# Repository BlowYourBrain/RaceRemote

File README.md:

# RaceRemote

Текущая сборка: [плата 0.3, отдельный общий провод XIAO и карта подключений](cad/xiao-return-h10/README.md).

Последняя примерка: [провода мотора и обнаруженный конфликт резерва клеммы с подвеской](cad/motor-harness/README.md).

Текущий вариант внутреннего питания: [CAD припаянной пары и крепления](cad/direct-logic-harness/README.md), включая ограничения прежней проводки.

Проект одинаковых радиоуправляемых машинок с управлением по Wi-Fi с телефона, сменными кузовами и опциональной камерой.

**Перед продолжением работы прочитайте [описание проекта и принятые решения](docs/project-brief.md).** Там собраны требования, имеющееся железо, результаты первичного аудита и вопросы, которые ещё предстоит решить.

**Ближайшие шаги к физической сборке:** [первый прототип](docs/first-prototype.md) — доступные устройства, недостающие данные и порядок радио/FPV, привода, механики и зарядки.

- [Стенд Android ↔ ESP32](docs/control-bench.md) — `vea.raceremote`, запуск и проверенные устройства.
- [Протокол Control v1](docs/control-v1.md) — команды, сессия и остановка.
- [Подготовка стенда привода](docs/drive-bench.md) — проект соединений TA6586, питание и проверка рулевого узла.
- [Контракты и их статус](docs/contracts.md) — согласованные требования и интерфейсы, которые предстоит определить.
- [Архитектура и known unknowns](docs/architecture-and-unknowns.md) — организация системы, открытые вопросы и способы их закрыть.
- [Кандидаты шасси](docs/chassis-candidates.md) — исходные проекты, ограничения и возможная адаптация под Wi-Fi.
- [Детали и цены](docs/parts.md) — предложения магазинов, количество на 1/4/6 машинок и незакрытые позиции.
- [Камера для FPV](docs/camera-candidates.md) — кандидаты и проверка задержки до выбора для серии.
- [Первый FPV-стенд](docs/fpv-bench.md) — состав, подключение и порядок измерений; предложение для покупки ещё подбирается.
- [USB-C: зарядка и прошивка](docs/usb-c-power.md) — отдельный удобный зарядный порт, ограничения для 2S и сервисный USB под кузовом.
- [Watchdog зарядного контроллера](hardware/charge-watchdog/README.md) — схема-кандидат и проверка удержания запрета при зависании MCU.
- [Зарядный MCU и согласование сигналов](hardware/charger-mcu/README.md) — CH32, аппаратный ARM/revoke/readback и доступ SWIO; схема без программы и монтажа.
- [Удерживаемая ошибка зарядного тока](hardware/charge-overcurrent/README.md) — INA300 и шунт, схема стенда и границы проверки.
- [Смена батареи и кузов](docs/battery-and-body.md) — три LW 601844HP, быстрое снятие кузова на магнитах и зарядка запасной батареи.
- [Правила работы агента](AGENTS.md) — обязательная фиксация ключевых моментов и контрактов по просьбе пользователя.

Репозитории:

- [RaceRemote](https://github.com/BlowYourBrain/RaceRemote) — Android-приложение и старые эксперименты с Arduino.
- [RC_CAR_ESP32](https://github.com/BlowYourBrain/RC_CAR_ESP32) — прошивка стенда ESP32 и старый эксперимент; приватный репозиторий.

Выбор серийных компонентов и электрическая схема пока не утверждены.

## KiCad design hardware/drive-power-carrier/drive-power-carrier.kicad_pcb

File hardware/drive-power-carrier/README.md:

# Общая плата привода и питания XIAO — предложение 0.3

**0.3, 15 сентября:** добавлена отдельная площадка H10 для общего провода XIAO; H5 остаётся силовым возвратом входного питания. Схема/PCB проходят ERC, DRC и parity: 26 позиций, 58 выводов, семь подмен цепей. Прежние 57 площадок и дорожки версии 0.2 сохранены, зоны меди пересчитаны. [Отчёт v03](../../docs/evidence/drive-power-carrier-v03/summary.json), [текущая проводка и карта площадок](../../cad/xiao-return-h10/README.md). Геометрическая проверка H10 и нового провода пройдена при 0/+3; ток/нагрев и физический монтаж не проверены. Ниже сведения о конструкции 0.2 остаются основанием; её отчёты исторические в `957e015`.

15 сентября 2026. Контракт **DRIVE-POWER-CARRIER-01 v0.2**. Это отдельный кандидат объединения [носителя TA6586](../motor-carrier/README.md) и [XIAO-LOGIC-01 v0.2](../xiao-logic-power/README.md). В 0.2 исправлены [площадки MAX40200 и резерв его корпуса](max40200-package.md); уведомление 2571C оказалось изменением транспортной упаковки. Исходные схемы сохранены. Изготовления, монтажа и физических испытаний ещё нет.

[Схема PDF](schematic.pdf) · [редактируемая схема](drive-power-carrier.kicad_sch) · [PCB KiCad](drive-power-carrier.kicad_pcb) · [верх](top.svg) · [низ, зеркальный вид](bottom.svg) · [BOM](bom.csv) · [все выводы](connections.csv) · [3D в машинке](../../cad/drive-power-carrier/viewer.html).

Размер PCB остался **30 × 18 × 1,6 мм**. Сохранились места всех 14 прежних позиций и геометрия их 27 площадок. Новые U2/U3, делитель и конденсаторы находятся снизу; нагрузочный R7 — сверху. Два прежних отрезка VM заменены обходом четырёх тепловых переходов U2. Остальные прежние дорожки сохранены. Вместо отдельной платы питания получилась одна плата с 25 позициями: 16 покупных компонентов и девять встроенных площадок для проводов.

| Площадка | Цепь и назначение |
|---|---|
| H1 / H2 | CMD_FI / CMD_BI: команды TA6586 через прежние резисторы |
| H3 / H5 | DRIVE_GND: общий провод привода и логики, не произвольная земля зарядника |
| H4 | VM: отдельно квалифицируемое питание мотора |
| H6 / H7 | FO / BO: выводы мотора |
| H8, новая | WAVE_5V: вход от Waveshare, условный расчётный диапазон 4,75…5,25 В |
| H9, новая | XIAO_BAT: выход через MAX40200 к BAT0 XIAO; не к выводу 5V/VBUS |
| H10, добавлена в 0.3 | DRIVE_GND: отдельная посадка провода GND0 XIAO; H5 освобождена для силового возврата |

Участники питания: Waveshare → U2 TPS73701DRBR → U3 MAX40200AUK+T → BAT0 XIAO. Общий провод XIAO/Waveshare приходит к DRIVE_GND. VM, WAVE_5V и XIAO_BAT — разные цепи. К новой плате не добавлен провод штатного USB VBUS. Сырой аккумулятор 2S нельзя подключать к H8/H9; объединение минусов батареи, защиты и USB зарядки требует отдельной согласованной схемы. Эта плата не заряжает LW и не заменяет его защиту.

Схема логики электрически повторяет v0.2 с перенумерацией: прежние U1/U2 → U2/U3; R1…R3 → R5…R7; C1…C4 → C3…C6; J1/J3 → H8/H9. Земляные J2/J5 заменены существующими H3/H5. U2 выдаёт номинально 3,997 В; R7=360 Ом обеспечивает предварительную нагрузку до обратного блокиратора. Для C4 требуется фактическая ёмкость ≥1 мкФ, для C5/C6 ≥0,33 мкФ каждого, полная ёмкость на выходе U3 ≤100 мкФ. Конкретные MLCC и их зависимость от напряжения ещё не выбраны.

При исчезновении питания логики аппаратная остановка здесь не доказана: сохраняются резисторы на входах TA6586 и программные правила остановки, но последовательность спадания шин, USB-переходы и ток мотора требуют стенда. MAX40200 имеет внутреннюю обратную блокировку; её реальные переходы и отказы платы пока не проверены.

Проверки KiCad 10.0.6: **ERC=0, DRC=0, несоединённых цепей=0, расхождений схемы и платы=0**. Независимый список сверяет 57 выводов, включая четыре NC, и 12 рабочих цепей; шесть намеренных подмен цепей обнаружены. Координаты CAD сверены с площадками и центрами новых компонентов PCB; размеры/шаг площадок U3 — с прочитанным чертежом. [Отчёт и хеши](../../docs/evidence/drive-power-carrier-v02/summary.json), [DRC с перечнем стандартно отключённых проверок](../../docs/evidence/drive-power-carrier-v02/drc.json). Это проверка проекта при выбранных правилах, не подтверждение его допустимого тока. Отчёты v01 относятся к прежней геометрии `c041b2b`.

Разводка предлагает минимальный зазор/ширину 0,15 мм, силовые дорожки прежнего носителя — 1,2 мм, новые основные линии питания — 0,4…0,6 мм. Четыре перехода под тепловой площадкой U2 имеют отверстие 0,3 мм и диаметр меди 0,6 мм. Изготовитель, толщина меди, обработка переходов, маска/паста и ручной монтаж не согласованы. Gerber для заказа не выпущен.

Открытые вопросы перед изготовлением:

- U2 DRB: посадка основана на TI Rev W, стр. 47–48; тепловая площадка обязательна. Заполнение/закрытие переходов и объём припоя нужно согласовать, иначе припой может уйти в отверстия.
- U3: корпус сверён с официальным 21-0057 K, площадки — с копией Maxim 90-0174 B. Актуальность редакции рисунка площадок у ADI и посадка реального компонента ещё не подтверждены. PIN2571C касается только транспортной упаковки.
- Тепло двух микросхем рядом с моторным драйвером. Прежний условный расчёт даёт около 0,513 Вт на проходном элементе U2 при 0,5 А и до 0,850 Вт в выбранном углу при 0,6 А, без собственного тока и переходных процессов. Сам факт наличия меди/переходов не доказывает допустимую температуру.
- Стабильность питания при работе камеры, пусках мотора/серво и подключении USB; реальные токи и допустимая нагрузка дорожек.
- Новые провода H8/H9, разгрузка пайки, установка/снятие платы и остальные положения регулировки.

Источники геометрии: [TPS737, TI Rev W](https://www.ti.com/lit/ds/symlink/tps737.pdf), [MAX40200, ADI Rev 4](https://www.analog.com/media/en/technical-documentation/data-sheets/max40200.pdf); исходные электрические расчёты и ограничения переноса падения напряжения SOT23 с 3,3 В на около 4 В — в [XIAO-LOGIC-01 v0.2](../xiao-logic-power/README.md). Новых цен и заказов этот BOM не подтверждает; имеющиеся ценовые наблюдения остаются в [таблице деталей](../../docs/parts.md).

Воспроизведение из корня репозитория, локальным Python KiCad:

```powershell
& build/tooling/kicad-10.0.6/bin/python.exe tools/build_drive_power_carrier.py
& build/tooling/kicad-10.0.6/bin/python.exe tools/verify_drive_power_carrier.py
uv run --with-requirements tools/cad-candidate-requirements.txt python tools/check_drive_power_fit.py
uv run --with-requirements tools/cad-candidate-requirements.txt python tools/build_drive_power_view.py
```

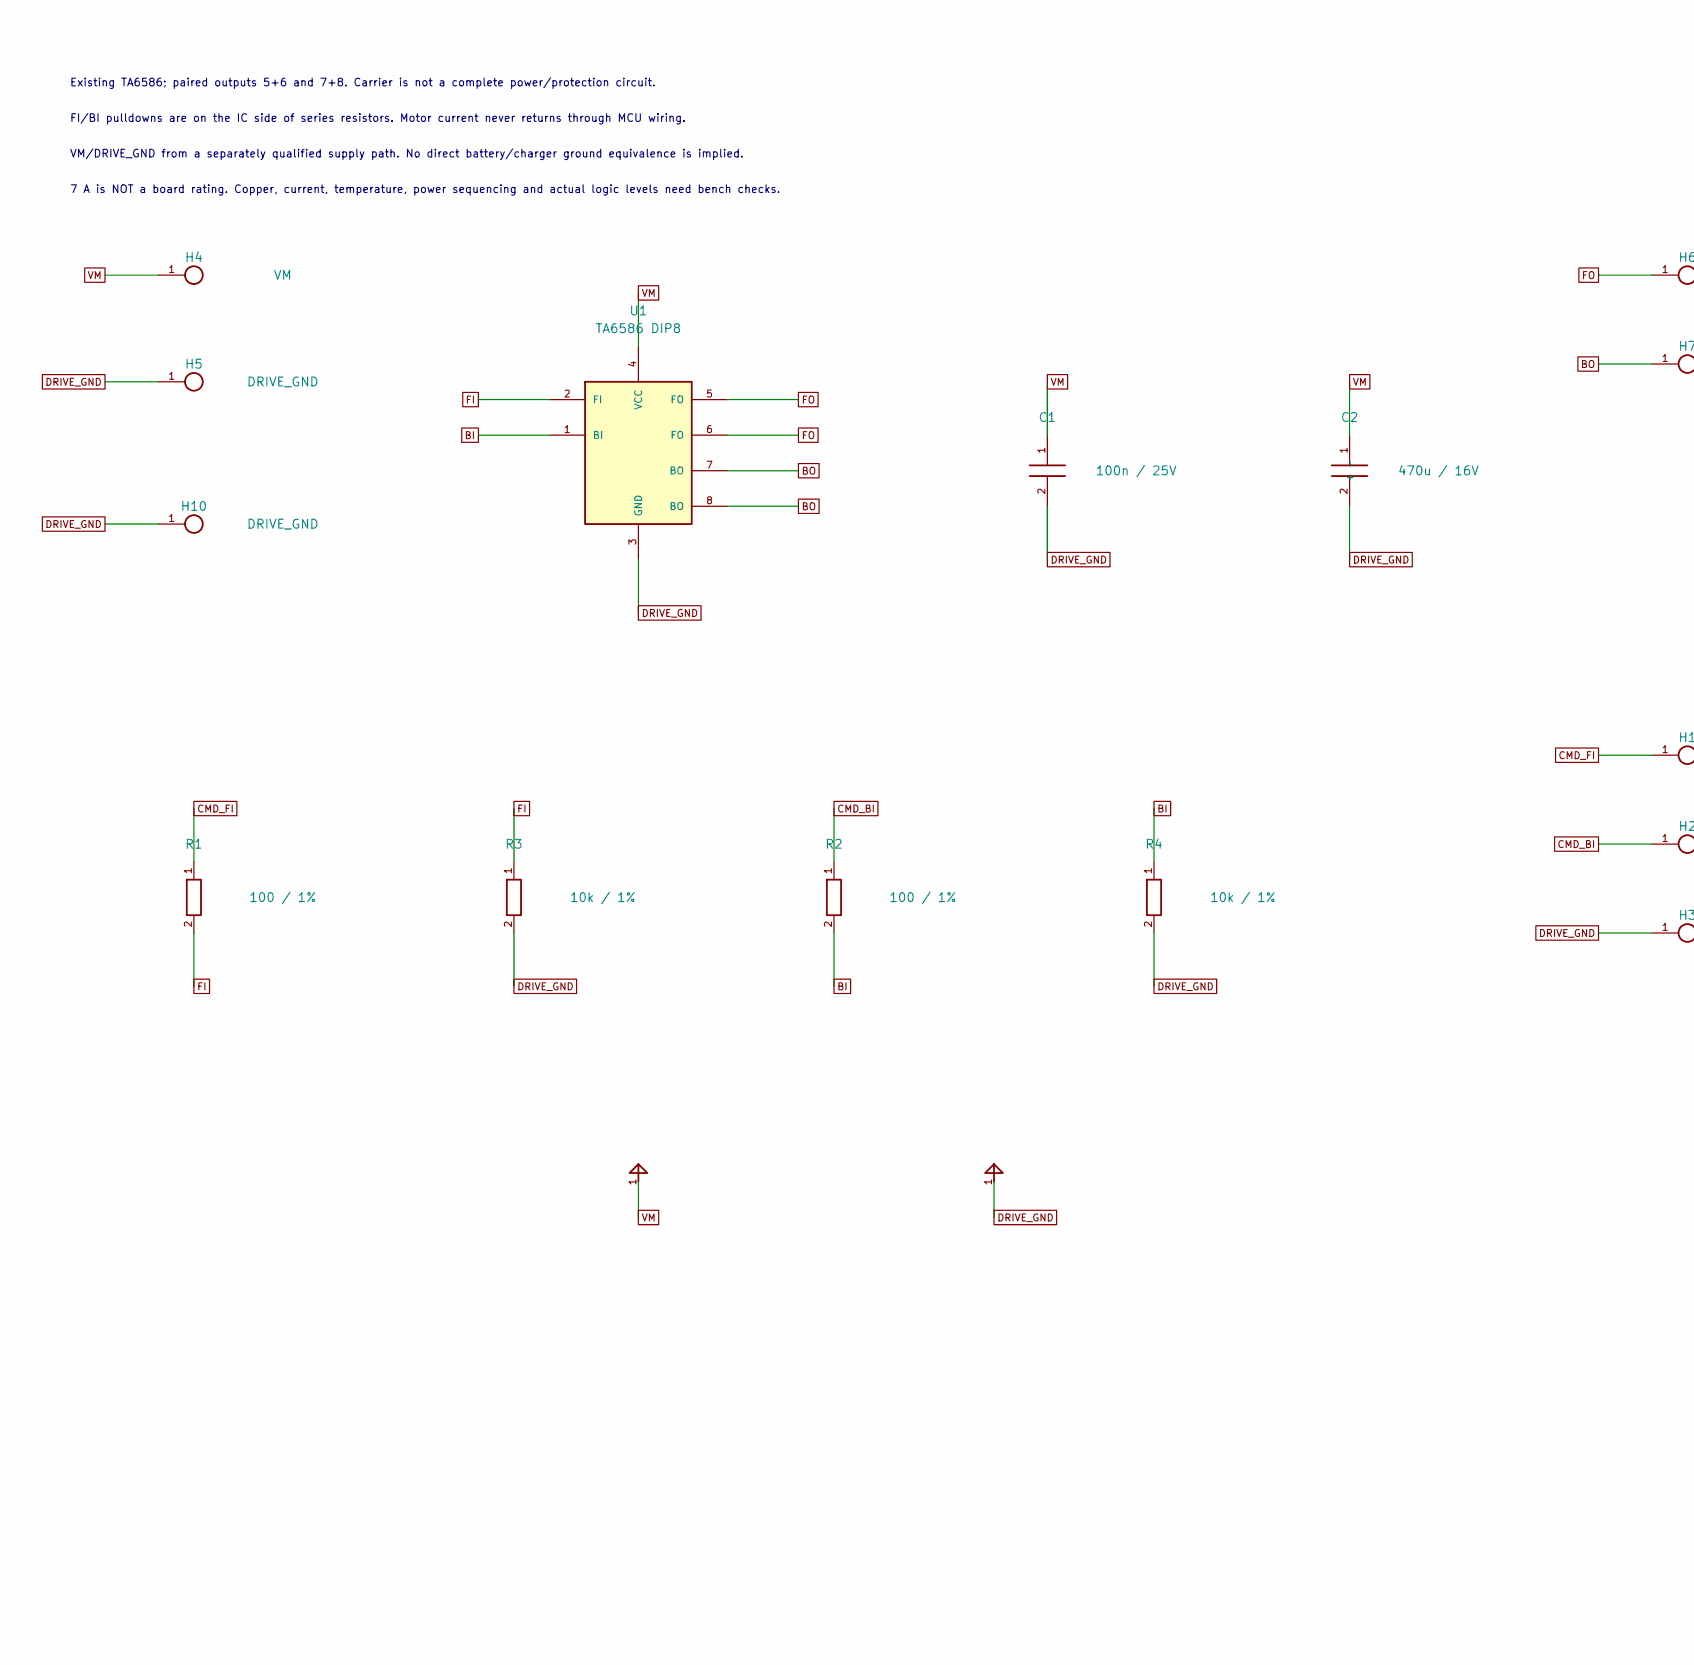
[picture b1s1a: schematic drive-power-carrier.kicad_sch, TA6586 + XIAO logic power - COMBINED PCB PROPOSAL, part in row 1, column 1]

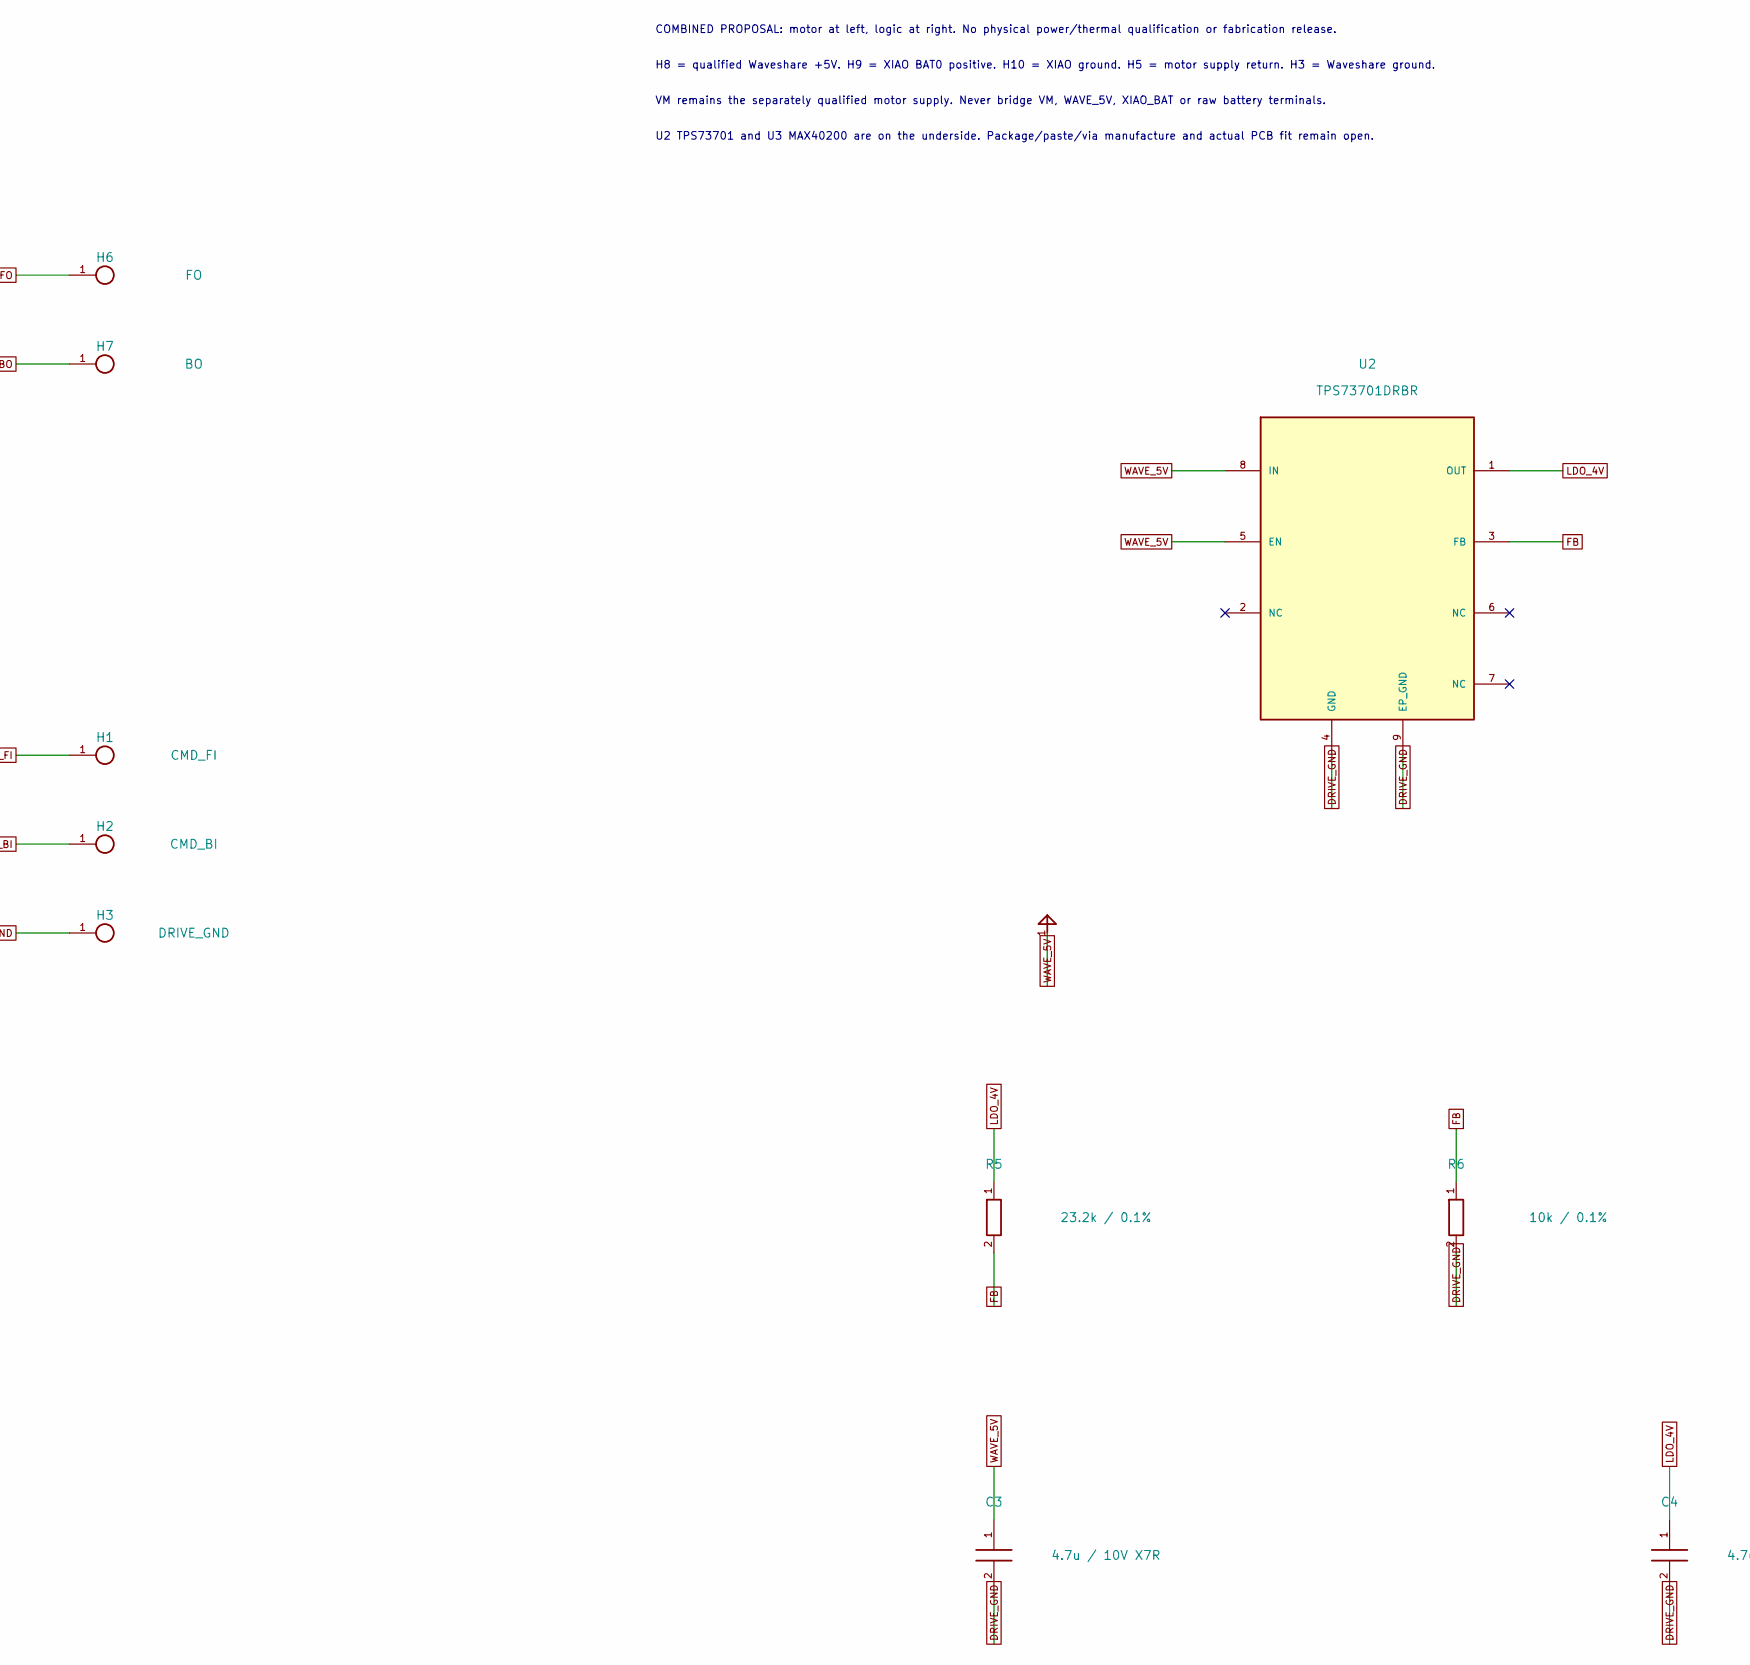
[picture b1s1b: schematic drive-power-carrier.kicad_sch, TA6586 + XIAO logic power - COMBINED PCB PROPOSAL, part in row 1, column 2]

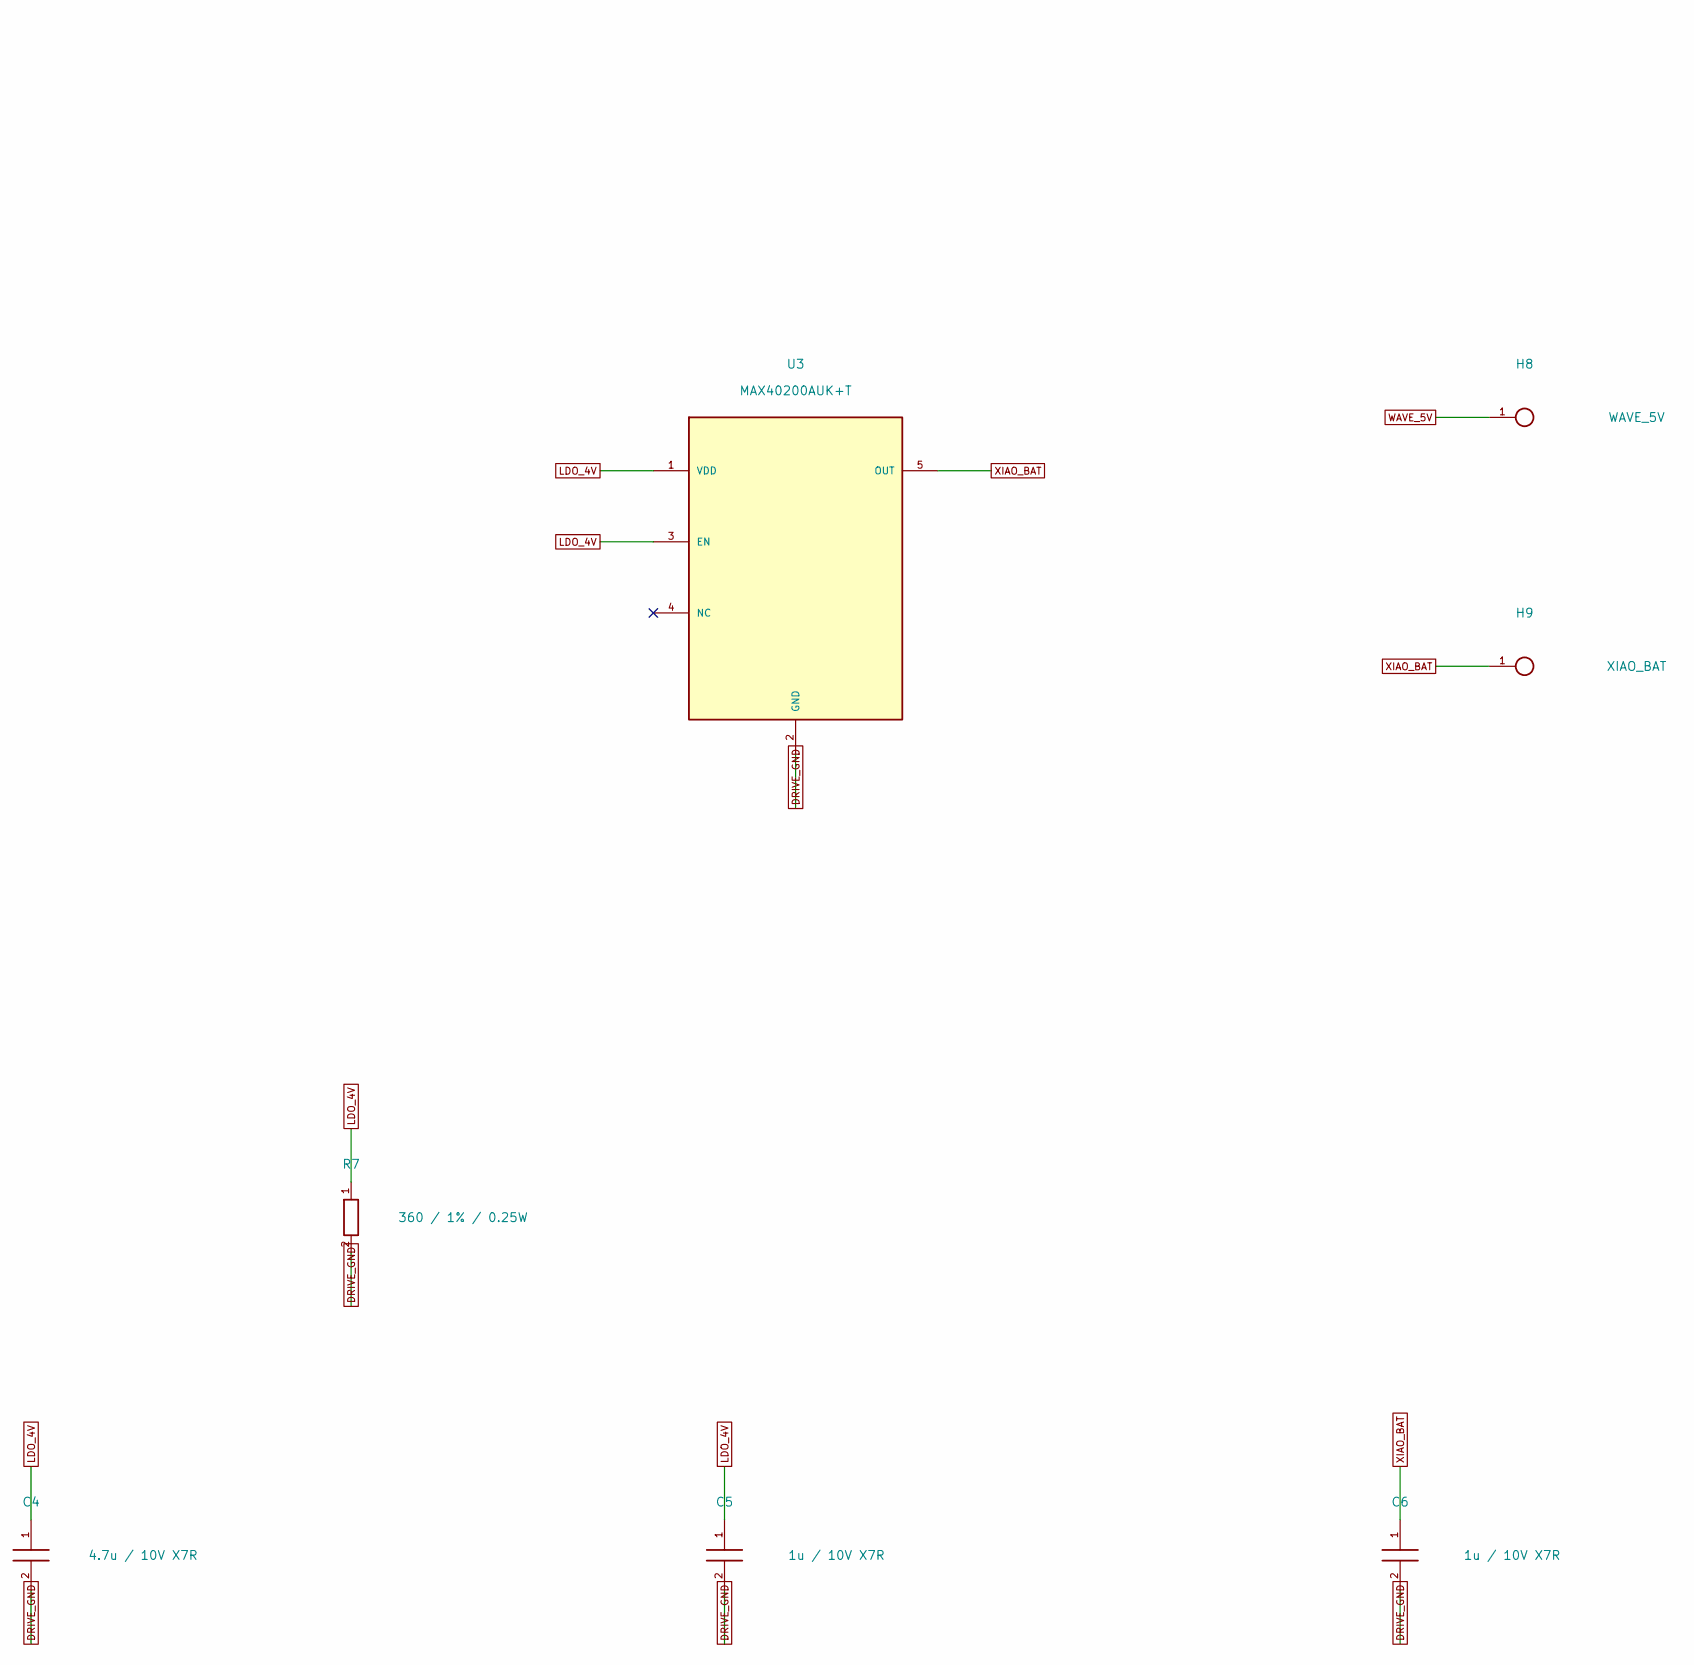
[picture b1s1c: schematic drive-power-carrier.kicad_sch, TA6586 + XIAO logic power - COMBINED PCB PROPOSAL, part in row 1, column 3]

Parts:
C1: 100n / 25V; C_0805
C2: 470u / 16V; CP_D8_P3.5
C3: 4.7u / 10V X7R; C_0805_C3
C4: 4.7u / 10V X7R; C_0805_C4
C5: 1u / 10V X7R; C_0805_C5
C6: 1u / 10V X7R; C_0805_C6
H1: CMD_FI; WirePad_1mm
H2: CMD_BI; WirePad_1mm
H3, H5: DRIVE_GND; WirePad_1mm
H4: VM; WirePad_1mm
H6: FO; WirePad_1mm
H7: BO; WirePad_1mm
H8: WAVE_5V; WirePad_1mm_H8
H9: XIAO_BAT; WirePad_1mm_H9
H10: DRIVE_GND; WirePad_1mm_H10
R1, R2: 100 / 1%; R_0805
R3, R4: 10k / 1%; R_0805
R5: 23.2k / 0.1%; R_0805_R5
R6: 10k / 0.1%; R_0805_R6
R7: 360 / 1% / 0.25W; R_1206_R7
U1: TA6586 DIP8; TA6586_DIP8
U2: TPS73701DRBR; TPS73701_DRB_3x3_EP_U2
U3: MAX40200AUK+T; SOT23_5_ADI_90_0174_B_U3

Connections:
BI: R2.2, R4.1, U1.1 (BI)
BO: H7.1, U1.7 (BO), U1.8 (BO)
CMD_BI: H2.1, R2.1
CMD_FI: H1.1, R1.1
DRIVE_GND: C1.2, C2.2 (-), C3.2, C4.2, C5.2, C6.2, H3.1, H5.1, H10.1, R3.2, R4.2, R6.2, R7.2, U1.3 (GND), U2.4 (GND), U2.9 (EP_GND), U3.2 (GND)
FB: R5.2, R6.1, U2.3 (FB)
FI: R1.2, R3.1, U1.2 (FI)
FO: H6.1, U1.5 (FO), U1.6 (FO)
LDO_4V: C4.1, C5.1, R5.1, R7.1, U2.1 (OUT), U3.1 (VDD), U3.3 (EN)
VM: C1.1, C2.1 (+), H4.1, U1.4 (VCC)
WAVE_5V: C3.1, H8.1, U2.5 (EN), U2.8 (IN)
XIAO_BAT: C6.1, H9.1, U3.5 (OUT)

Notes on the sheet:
Existing TA6586; paired outputs 5+6 and 7+8. Carrier is not a complete power/protection circuit.
FI/BI pulldowns are on the IC side of series resistors. Motor current never returns through MCU wiring.
VM/DRIVE_GND from a separately qualified supply path. No direct battery/charger ground equivalence is implied.
7 A is NOT a board rating. Copper, current, temperature, power sequencing and actual logic levels need bench checks.
COMBINED PROPOSAL: motor at left, logic at right. No physical power/thermal qualification or fabrication release.
H8 = qualified Waveshare +5V. H9 = XIAO BAT0 positive. H10 = XIAO ground. H5 = motor supply return. H3 = Waveshare ground.
VM remains the separately qualified motor supply. Never bridge VM, WAVE_5V, XIAO_BAT or raw battery terminals.
U2 TPS73701 and U3 MAX40200 are on the underside. Package/paste/via manufacture and actual PCB fit remain open.

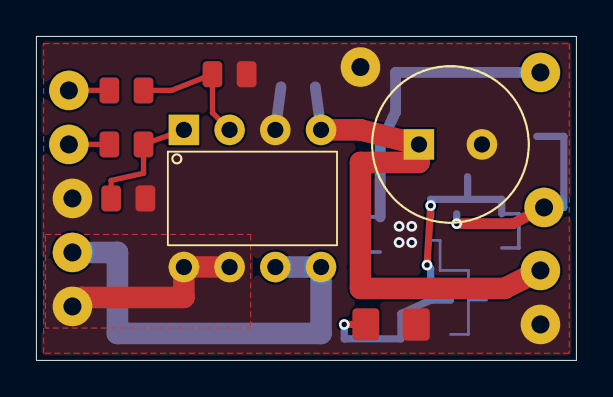
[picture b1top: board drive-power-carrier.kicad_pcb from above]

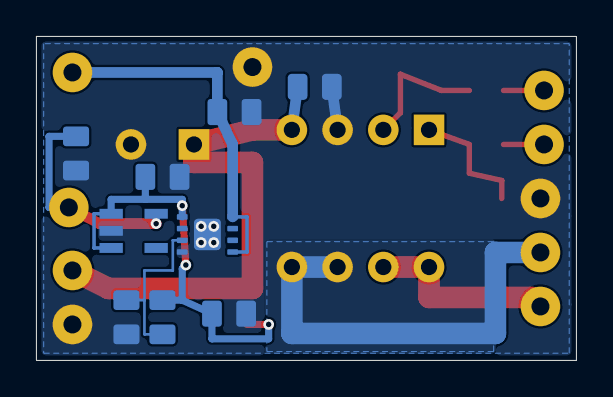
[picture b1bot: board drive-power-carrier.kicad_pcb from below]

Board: 2 copper layers, 30.0 x 18.0 mm, 26 parts (9 on the bottom side), 12 nets.

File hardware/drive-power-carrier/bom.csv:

reference,value,footprint,side,mpn_reference,status
C1,100n / 25V,RaceRemote_Motor:C_0805,B,,Candidate; not purchased
C2,470u / 16V,RaceRemote_Motor:CP_D8_P3.5,F,16ZLH470MEFC8X11.5,Candidate; not purchased
C3,4.7u / 10V X7R,RaceRemote_DrivePower:C_0805_C3,B,,Candidate; not purchased
C4,4.7u / 10V X7R,RaceRemote_DrivePower:C_0805_C4,B,,Candidate; not purchased
C5,1u / 10V X7R,RaceRemote_DrivePower:C_0805_C5,B,,Candidate; not purchased
C6,1u / 10V X7R,RaceRemote_DrivePower:C_0805_C6,B,,Candidate; not purchased
H1,CMD_FI,RaceRemote_Motor:WirePad_1mm,F,,Integral PCB solder pad; not purchased connector
H10,DRIVE_GND,RaceRemote_DrivePower:WirePad_1mm_H10,F,,Integral PCB solder pad; not purchased connector
H2,CMD_BI,RaceRemote_Motor:WirePad_1mm,F,,Integral PCB solder pad; not purchased connector
H3,DRIVE_GND,RaceRemote_Motor:WirePad_1mm,F,,Integral PCB solder pad; not purchased connector
H4,VM,RaceRemote_Motor:WirePad_1mm,F,,Integral PCB solder pad; not purchased connector
H5,DRIVE_GND,RaceRemote_Motor:WirePad_1mm,F,,Integral PCB solder pad; not purchased connector
H6,FO,RaceRemote_Motor:WirePad_1mm,F,,Integral PCB solder pad; not purchased connector
H7,BO,RaceRemote_Motor:WirePad_1mm,F,,Integral PCB solder pad; not purchased connector
H8,WAVE_5V,RaceRemote_DrivePower:WirePad_1mm_H8,F,,Integral PCB solder pad; not purchased connector
H9,XIAO_BAT,RaceRemote_DrivePower:WirePad_1mm_H9,F,,Integral PCB solder pad; not purchased connector
R1,100 / 1%,RaceRemote_Motor:R_0805,F,,Candidate; not purchased
R2,100 / 1%,RaceRemote_Motor:R_0805,F,,Candidate; not purchased
R3,10k / 1%,RaceRemote_Motor:R_0805,F,,Candidate; not purchased
R4,10k / 1%,RaceRemote_Motor:R_0805,F,,Candidate; not purchased
R5,23.2k / 0.1%,RaceRemote_DrivePower:R_0805_R5,B,,Candidate; not purchased
R6,10k / 0.1%,RaceRemote_DrivePower:R_0805_R6,B,,Candidate; not purchased
R7,360 / 1% / 0.25W,RaceRemote_DrivePower:R_1206_R7,F,,Candidate; not purchased
U1,TA6586 DIP8,RaceRemote_Motor:TA6586_DIP8,F,TA6586,Existing inventory
U2,TPS73701DRBR,RaceRemote_DrivePower:TPS73701_DRB_3x3_EP_U2,B,TPS73701DRBR,Candidate; not purchased
U3,MAX40200AUK+T,RaceRemote_DrivePower:SOT23_5_ADI_90_0174_B_U3,B,MAX40200AUK+T,Candidate; not purchased

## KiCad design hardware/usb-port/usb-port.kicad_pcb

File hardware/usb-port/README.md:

# Пассивная плата зарядного USB-C, ревизия 0.2

14 сентября 2026. **Схема и разводка выполнены, ERC/DRC и сравнение схемы с PCB прошли, плата не изготовлена.** Это плата разъёма с двумя резисторами, подключаемая к отдельному зарядному узлу. Зарядного контроллера, защиты аккумулятора, ограничения входного тока и согласования PD/QC здесь нет. Батарею 2S к VBUS не подключать.

[Открыть PCB](usb-port.kicad_pcb) · [Проект KiCad](usb-port.kicad_pro) · [CAD-размещение](../../cad/usb-port-study.md) · [Проверка DRC](../../docs/evidence/usb-port-pcb-drc.json)

[Схема KiCad](usb-port.kicad_sch) · [Схема PDF](schematic.pdf) · [ERC](../../docs/evidence/usb-port-erc.json) · [Проверка соединений и намеренных ошибок](../../docs/evidence/usb-port-pcb-verification.json)

Плата двухслойная, **26×7,6×1 мм**. Медь 35 мкм предложена для изготовления и использована в CAD; полный стек слоёв с изготовителем ещё не согласован. Разъём GCT USB4105-GF-A сверху, R1/R2 5,1 кОм ±1% типоразмера 0603 снизу. Два отверстия Ø2,4 мм с зонами без меди радиусом 2,5 мм под металлический крепёж. Шесть площадок Ø1,6 с отверстиями Ø0,8 — для пайки жгута; разъём жгута/калибр провода пока не выбраны. Крепление должно разгружать жгут от натяжения, его конструкция ещё открыта.

При сверке с библиотекой обнаружено: в прежнем CAD при X входа 58,5 мм задние площадки USB выходили за плату на 0,33 мм. Сдвиг входа до X=59,1 мм даёт зазор меди до заднего края **0,27 мм**. Ширина платы в CAD увеличена с 22 до 26 мм для пайки жгута за пределами крепёжных зон. Передняя кромка PCB осталась X=58,5 мм: корпус разъёма выступает за неё на 0,6 мм; отдельный вырез под вход не потребовался. [Геометрия площадок и отверстий](geometry.json) экспортируется из KiCad в OpenSCAD.

## USB-PORT-01, предложение v0.2

Участники: зарядный USB-C ↔ плата порта ↔ жгут ↔ отдельный зарядник. Штатный сервисный USB XIAO к этой плате не подключается.

| Контакт | Цепь | Назначение |
| --- | --- | --- |
| H1 | VBUS | Вход от USB-источника; цель системы — 5 В. К защите/ограничителю входа зарядника |
| H2 | DP | A6/B6 разъёма, линия определения источника |
| H3 | CC1 | A5, отдельный R1 5,1 кОм на GND |
| H4 | GND | Общий провод USB и экран разъёма |
| H5 | DM | A7/B7 разъёма, линия определения источника |
| H6 | CC2 | B5, отдельный R2 5,1 кОм на GND |

На рисунках сверху вниз слева H1/H2/H3, справа H4/H5/H6. Низ показан **без зеркалирования** для сопоставления слоёв, а не как вид при перевороте платы. Сверять маркировку цепей в KiCad перед пайкой; маркировка выводов на самой плате пока не добавлена.

CC1 и CC2 не соединяются друг с другом. На основной плате допускаются только подходящие высокоомные входы измерения CC, в том числе при её обесточивании; вторая пара Rd недопустима. Их допустимые напряжения и защита ещё определить. Резисторы позволяют источнику обнаружить потребитель, но **не разрешают произвольный ток**. Определение доступного тока, защита от ESD/замыканий, запрет заряда при ошибках и защита от обратного питания остаются в проектировании зарядного узла. D+/D− разведены для определения источника; USB 2.0 передача данных, импеданс пары и высокоскоростной интерфейс не заявлены.

Обрыв жгута, одного Rd или неправильное распознавание источника должны приводить к запрету заряда либо к подтверждённому допустимому режиму основной платы. Здесь MCU/логики разрешения нет. При отключении VBUS заряд прекращает основной узел; сам порт не разрешает движение.

Основание для двух Rd: [Renesas, модель USB Type-C Source/Sink, рисунки 5–6](https://www.renesas.com/en/support/engineer-school/usb-power-delivery-03). Распиновка J1 — [GCT USB4105 B4](https://gct.co/files/drawings/usb4105.pdf). A8/B8 (SBU) оставлены без подключений.

## Проверка и её пределы

KiCad **10.0.6**: DRC с повторной заливкой зон — 0 нарушений и 0 неподключённых соединений. Заданные минимумы: дорожка/межцепной зазор 0,15 мм, зазор меди до края 0,20 мм, зазор до отверстия 0,15 мм, переход Ø0,50 с отверстием Ø0,25 мм. Зазор до отверстия выбран с учётом заводского посадочного места: там есть около 0,194 мм до направляющего отверстия. Возможности конкретного изготовителя ещё не подтверждены.

В отчётах сохранены стандартные отключённые проверки KiCad; у площадок жгута и крепёжных отверстий нет отдельных courtyard. Их механические зоны проверяются явно в PCB/CAD. Исключения для получения нуля не добавлялись. **ERC: 0 замечаний; сравнение схемы с PCB: 0 расхождений.** Дополнительно сверены 27 логических выводов экспортированного netlist с площадками PCB, включая повторные контакты питания и экрана. В отдельных копиях намеренно перепутан H3 с CC2 и удалён R1: сравнение обнаруживает соответственно `net_conflict` и `missing_footprint`.

Схема задаёт соединения самостоятельно, без чтения цепей PCB. Символ USB взят из KiCad 10.0.6, обозначение экрана адаптировано `SH` → `S1` под GCT; происхождение и изменения — в [NOTICE](SYMBOLS-NOTICE.md). Для A8/B8 созданы явные NC-цепи KiCad, проводников на них нет. R1: контакт 1 → GND, 2 → CC1; R2: 1 → CC2, 2 → GND. UUID связывают символы с посадочными местами. Изменение 0.2 затрагивает электрические метаданные PCB; расположение и размеры площадок/отверстий сохранены, 42 записи CAD проверены по текущей плате.

ERC/DRC не доказывают допустимый ток/нагрев, отсутствие дефектов пайки, стойкость к статике и работоспособность зарядки. Зарядный узел 2S, крепление жгута и физические измерения остаются открытыми.

Приёмка изготовленного образца: прозвонить пары силовых контактов и экран, отсутствие коротких между VBUS/GND/DP/DM/CC; проверить каждый Rd около 5,1 кОм (при отключённом заряднике). Затем проверить 5-В источник с ограничением тока и обе ориентации A–C/C–C, падение напряжения/нагрев при выбранном токе, крепление и жгут. Эти измерения не выполнены.

## Воспроизведение

Используется Python из KiCad, обычный Python не содержит `pcbnew`:

```powershell
& build/tooling/kicad-10.0.6/bin/python.exe tools/build_usb_port_pcb.py
& build/tooling/kicad-10.0.6/bin/python.exe tools/build_usb_port_schematic.py
& build/tooling/kicad-10.0.6/bin/python.exe tools/verify_usb_port.py
& build/tooling/kicad-10.0.6/bin/kicad-cli.exe sch export pdf hardware/usb-port/usb-port.kicad_sch -o hardware/usb-port/schematic.pdf
uv run --with-requirements tools/cad-requirements.txt python tools/build_usb_port_study.py
```

`verify_usb_port.py` запускает штатные ERC/DRC с `--schematic-parity`, проверяет все разделы JSON независимо от кода возврата CLI, сопоставляет netlist/PCB и проверяет две намеренные ошибки в `build/usb-port-pcb/negative-controls/`. На физические устройства скрипт не воздействует. Для просмотра схемы достаточно проектных библиотек; повторно извлекать полные библиотеки KiCad не нужно. Генератор формата схемы основан на [официальном описании KiCad](https://dev-docs.kicad.org/en/file-formats/sexpr-schematic/).

На этом ПК KiCad извлечён в игнорируемую папку `build/tooling/kicad-10.0.6` из [официального подписанного дистрибутива](https://kicad-downloads.s3.cern.ch/windows/stable/kicad-10.0.6-x86_64.exe). Проверена действительная подпись KICAD SERVICES CORPORATION. Системная установка не выполнялась. Извлечены `bin/*`, `lib/*`, `share/kicad/schemas/*`, `share/kicad/template/*`, `share/kicad/scripting/*` и используемый footprint резистора. На другом ПК можно использовать обычную установку KiCad 10.0.6, изменив пути.

Источники посадочных мест и лицензия — [NOTICE](RaceRemote_USB.pretty/NOTICE.md). Полная стоимость PCB/монтажа, производитель и жгут не выбраны. Разъём есть в [таблице предложений](../../docs/charge-parts.md); резисторы пока указаны как тип/номинал без проверенной цены. Заказов нет.

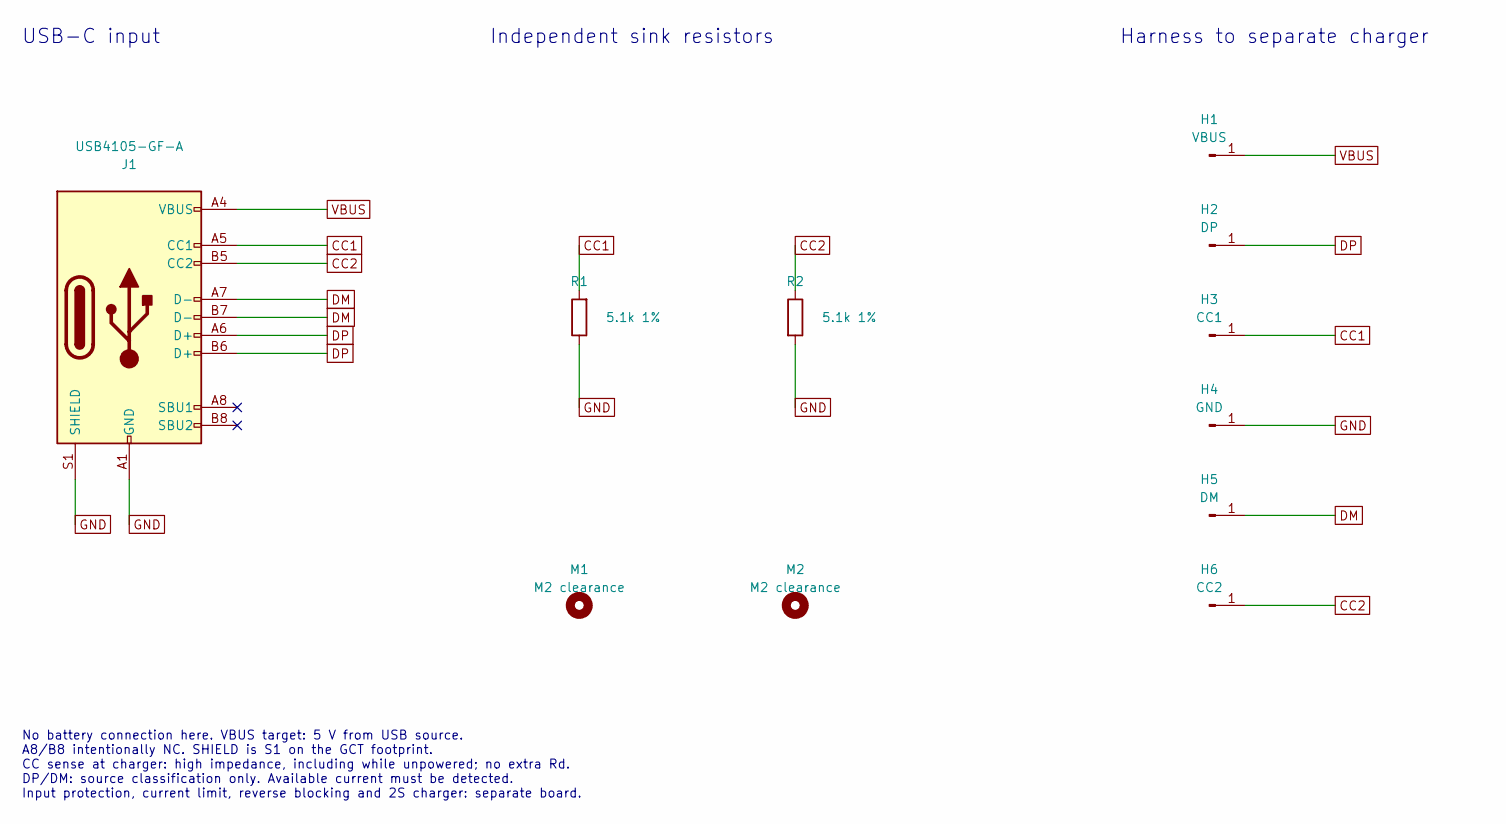
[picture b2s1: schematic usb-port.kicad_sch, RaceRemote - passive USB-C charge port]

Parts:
H1: VBUS; WirePad_D0.8mm
H2: DP; WirePad_D0.8mm
H3: CC1; WirePad_D0.8mm
H4: GND; WirePad_D0.8mm
H5: DM; WirePad_D0.8mm
H6: CC2; WirePad_D0.8mm
J1: USB4105-GF-A; USB_C_Receptacle_GCT_USB4105-xx-A_16P_TopMnt_Horizontal
M1, M2: M2 clearance; MountingHole_2.4mm
R1, R2: 5.1k 1%; R_0603_1608Metric

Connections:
CC1: H3.1, J1.A5 (CC1), R1.2
CC2: H6.1, J1.B5 (CC2), R2.1
DM: H5.1, J1.A7 (D-), J1.B7 (D-)
DP: H2.1, J1.A6 (D+), J1.B6 (D+)
GND: H4.1, J1.A1 (GND), J1.A12 (GND), J1.B1 (GND), J1.B12 (GND), J1.S1 (SHIELD), R1.1, R2.2
VBUS: H1.1, J1.A4 (VBUS), J1.A9 (VBUS), J1.B4 (VBUS), J1.B9 (VBUS)

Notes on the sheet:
USB-C input
Independent sink resistors
Harness to separate charger
No battery connection here. VBUS target: 5 V from USB source. A8/B8 intentionally NC. SHIELD is S1 on the GCT footprint. CC sense at charger: high impedance, including while unpowered; no extra Rd. DP/DM: source classification only. Available current must be detected. Input protection, current limi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

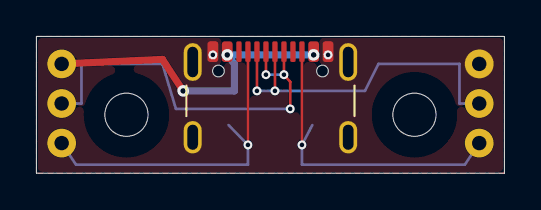
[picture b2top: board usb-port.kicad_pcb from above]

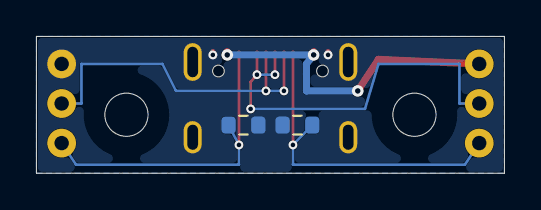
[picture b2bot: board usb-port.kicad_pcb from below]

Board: 2 copper layers, 26.0 x 7.6 mm, 11 parts (2 on the bottom side), 6 nets.

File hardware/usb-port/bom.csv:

Reference;Quantity_per_car;Description;Footprint;Purchase_status
J1;1;GCT USB4105-GF-A;USB_C_Receptacle_GCT_USB4105-xx-A_16P_TopMnt_Horizontal;Offers in docs/charge-parts.md - not ordered
R1 R2;2;5.1k ohm 1 percent 0603;R_0603_1608Metric;Exact manufacturer and offer unselected
PCB;1;2 layers 26x7.6 mm thickness 1 mm copper 35um;;Fabricator and cost unselected
H1 H2 H3 H4 H5 H6;0;Integrated solder pads - six wires required;;Wire specification and strain relief unselected
M1 M2;0;Integrated 2.4 mm mounting holes - M2 hardware required;;Screw length and nut type not finalized

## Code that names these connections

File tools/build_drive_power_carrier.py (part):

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        graphic(f, p.SHAPE_T_RECT, (x-w/2,y-h/2), (x+w/2,y+h/2), p.B_Fab if back else p.F_Fab)
        graphic(f, p.SHAPE_T_RECT, (x-w/2-margin,y-h/2-margin), (x+w/2+margin,y+h/2+margin), p.B_CrtYd if back else p.F_CrtYd, .05)
    u = new('U2', 'TPS73701DRBR', 20.5, 11, body=(3.1,3.1), height=1.05)
    mapping = {1:'LDO_4V',2:None,3:'FB',4:'DRIVE_GND',5:'WAVE_5V',6:None,7:None,8:'WAVE_5V'}
    for pin, dx, dy in [(1,1.4,-.975),(2,1.4,-.325),(3,1.4,.325),(4,1.4,.975),
                        (5,-1.4,.975),(6,-1.4,.325),(7,-1.4,-.325),(8,-1.4,-.975)]:
        pad(u,pin,mapping[pin],20.5+dx,11+dy,.6,.31)
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    # ADI 21-0057 K: D/E max3mm plus conservative .25mm protrusion each side.
    # Land pattern 90-0174 B: rectangular1.30x.55, row spacing2.50, pitch.95mm.
    u = new('U3','MAX40200AUK+T',24.6,10.8,body=(3.5,3.5),height=1.5)
    for pin,dx,dy,net in [(1,1.25,-.95,'LDO_4V'),(2,1.25,0,'DRIVE_GND'),(3,1.25,.95,'LDO_4V'),(4,-1.25,.95,None),(5,-1.25,-.95,'XIAO_BAT')]:
        pad(u,pin,net,24.6+dx,10.8+dy,1.3,.55)
    for a in u.Pads(): a.SetShape(p.PAD_SHAPE_RECT)
    outline(u,24.6,10.8,3.5,3.5,.25)
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
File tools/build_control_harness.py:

"""Route three proposed insulated control leads from referenced copper pads."""
import base64
import csv
import hashlib
import json
from pathlib import Path
import numpy as np
import trimesh
from build_packaging_v05 import mesh,intersect,tube
from layout_zcar_battery import box

ROOT=Path(__file__).resolve().parents[1]
DEST=ROOT/'cad/control-harness'
MOUNT=ROOT/'cad/motor-carrier-mount'


def main():
    reference=DEST/'xiao-pad-reference.json';pinref=json.loads(reference.read_text())
    pads={k:v['candidate_xyz_mm'] for k,v in pinref['pads'].items()}
    boardpath=ROOT/'hardware/motor-carrier/geometry.json';board=json.loads(boardpath.read_text())
    end={p['ref']:[25.75+p['xy_mm'][1],47+p['xy_mm'][0],31.1]for p in board['pads']if p['ref'].startswith('H')}
    routes={
      'FI':{'xiao':'D0','gpio':1,'terminal':'H1','net':'CMD_FI','color':[.9,.5,.05],
        'points_mm':[pads['D0'],[30.96583,87.1,23.17],[30.96583,87.1,37.3],[37.5,87.1,37.3],
                     [37.5,64,37.3],[28.75,64,37.3],[28.75,48.8,37.3],end['H1']]},
      'BI':{'xiao':'D1','gpio':2,'terminal':'H2','net':'CMD_BI','color':[.3,.3,.85],
        'points_mm':[pads['D1'],[28.42583,88.2,23.27],[28.42583,88.2,37.3],[38.6,88.2,37.3],
                     [38.6,63,37.3],[31.75,63,37.3],[31.75,48.8,37.3],end['H2']]},
      'GND':{'xiao':'GND','gpio':None,'terminal':'H3','net':'DRIVE_GND','color':[.18,.18,.2],
        # Shift solder target .25mm inward within the1.4mm ground pad, below clamp finger.
        'points_mm':[[pads['GND'][0],83.25,38.26],[28.42583,85,38.26],[28.42583,85.8,38.7],[38,89.5,38.7],
                     [39.7,89.5,38.7],[39.7,79,37.3],[39.7,62,37.3],
                     [34.75,62,37.3],[34.75,49,37.3],end['H3']]}}
    for r in routes.values():
        r['radius_mm']=.4
        r['centerline_length_mm']=round(float(np.linalg.norm(np.diff(r['points_mm'],axis=0),axis=1).sum()),3)
        assert next(p for p in board['pads']if p['ref']==r['terminal'])['net']==r['net']
    wires={n:tube(r['points_mm'],r['radius_mm'])for n,r in routes.items()}
    for n,m in wires.items():assert m.is_volume,n
    sources=[Path(__file__),reference,boardpath,ROOT/'tools/build_packaging_v05.py',ROOT/'tools/layout_zcar_battery.py']
    previous_path=ROOT/'docs/evidence/motor-carrier-mount-v01.json';sources.append(previous_path)
    previous=json.loads(previous_path.read_text())
    obstacles={}
    def add(path):
        sources.append(path);obstacles[path.relative_to(ROOT).as_posix()]=mesh(path)
        assert obstacles[path.relative_to(ROOT).as_posix()].is_volume,path
    for p in previous['source_sha256']:
        path=ROOT/p
        if path.suffix=='.stl' and path.name not in ['tray.stl','pads.stl','adjustable-cavity.stl']:
            add(path)
    for n in ['tray','clamp','nuts','screws','pads']:add(MOUNT/(n+'.stl'))
    xiao_path=ROOT/'docs/evidence/xiao-mount-v01.json';sources.append(xiao_path)
    boxes=json.loads(xiao_path.read_text())['source_bounding_boxes_mm']
    contact_masks=[box([1.6,1.0,1.6],r['points_mm'][0])for r in routes.values()]
    for n,b in boxes.items():
        m=box(np.diff(b,axis=0)[0],np.mean(b,axis=0))
        if n=='37':
            # Only local contact windows on the unperforated reference PCB box are omitted.
            m=trimesh.boolean.difference([m,*contact_masks],engine='manifold')
        obstacles['xiao-solid-'+n]=m
    cavity_path=ROOT/'cad/packaging-v05/inputs/adjustable-cavity.stl';sources.append(cavity_path);cavity=mesh(cavity_path)
    collisions={n:{o:intersect(m,om)for o,om in obstacles.items()}for n,m in wires.items()}
    pairs={n+'/'+o:intersect(wires[n],wires[o])for i,n in enumerate(wires)for o in list(wires)[i+1:]}
    outside={n:float(trimesh.boolean.difference([m,cavity],engine='manifold').volume)for n,m in wires.items()}
    assert all(np.isfinite(v)for group in collisions.values()for v in group.values())
    assert all(np.isfinite(v)for v in [*pairs.values(),*outside.values()])
    # Positive control: a straight shortcut from D0 toH1 crosses solid structure.
    shortcut=tube([routes['FI']['points_mm'][0],end['H1']],.4)
    shortcut_hits={n:intersect(shortcut,m)for n,m in obstacles.items()}
    report={'version':'0.1','date':'2026-09-15','pose_mm':[0,3],'routes':routes,
      'obstacle_hits_mm3':{n:{o:round(v,5)for o,v in group.items()if v>.001}for n,group in collisions.items()},
      'wire_pair_hits_mm3':{n:round(v,5)for n,v in pairs.items()if v>.001},
      'outside_body_mm3':{n:round(v,5)for n,v in outside.items()if v>.001},
      'straight_shortcut_positive_control':{n:round(v,5)for n,v in shortcut_hits.items()if v>.001},
      'contact_exception':'Only XIAO PCB solid37 within1.6x1x1.6mm boxes at the three proposed solder points',
      'physical_wiring':False,'power_domain_integration_verified':False,
      'strain_relief_designed':False,'connector_selected':False,'service_motion_with_wires_verified':False,
      'source_sha256':{p.relative_to(ROOT).as_posix():hashlib.sha256(p.read_bytes()).hexdigest()for p in sources}}
    out=ROOT/'docs/evidence/control-harness-v01.json'
    out.write_text(json.dumps(report,indent=2)+'\n',encoding='utf-8',newline='\n')
    print(json.dumps({k:report[k]for k in ['obstacle_hits_mm3','wire_pair_hits_mm3','outside_body_mm3','straight_shortcut_positive_control']},indent=2),flush=True)
    assert not any(report['obstacle_hits_mm3'].values())and not report['wire_pair_hits_mm3']and not report['outside_body_mm3']
    assert report['straight_shortcut_positive_control']
    for n,m in wires.items():m.export(DEST/(n+'.stl'))
    source=MOUNT/'viewer.html';text=source.read_text(encoding='utf-8')
    rows=json.loads(text.split('const parts=',1)[1].split(';\nconst adjustmentChecks=',1)[0])
    rows=[r for r in rows if r['id']!='wire-control']
    for n,m in wires.items():
        raw=np.hstack([m.triangles.reshape(-1,3),np.repeat(m.face_normals,3,axis=0)]).astype('<f4')
        rows.append(dict(id='control-'+n,label=n+' — XIAO '+routes[n]['xiao']+' → '+routes[n]['terminal'],
          color=routes[n]['color'],slide=None,level=0,wire=False,hidden=False,count=len(raw),data=base64.b64encode(raw.tobytes()).decode()))
    start=text.index('const parts=');endpos=text.index(';\nconst adjustmentChecks=',start)
    text=text[:start]+'const parts='+json.dumps(rows,ensure_ascii=False)+text[endpos:]
    text=text.replace('Крепление платы привода','Проводка управления')
    a=text.index('<p class="note">');b=text.index('</p>',a)
    text=text[:a]+'<p class="note">Три отдельных провода управления Ø0,8 мм: D0 → H1, D1 → H2, GND → H3. Координаты XIAO выведены из PCB1.5 и перенесены в STEP2023; ревизия полученной платы ещё неизвестна. Проверена только начальная геометрия 0/+3. Фиксация жгута, разъём и обслуживание с проводами ещё открыты; питание привода не подключено.'+text[b:]
    (DEST/'viewer.html').write_text(text,encoding='utf-8',newline='\n')
    with (DEST/'wiring.csv').open('w',encoding='utf-8-sig',newline='')as f:
        writer=csv.writer(f);writer.writerow(['signal','xiao_pad','gpio','carrier_pad','net','path_mm','wire_outer_diameter_mm','status'])
        for n,r in routes.items():writer.writerow([n,r['xiao'],r['gpio'],r['terminal'],r['net'],r['centerline_length_mm'],.8,'Proposal; not a cut length or verified wire SKU'])
    report['source_sha256'][source.relative_to(ROOT).as_posix()]=hashlib.sha256(source.read_bytes()).hexdigest()
    report['artifact_sha256']={p.relative_to(ROOT).as_posix():hashlib.sha256(p.read_bytes()).hexdigest()for p in [*sorted(DEST.glob('*.stl')),DEST/'viewer.html',DEST/'wiring.csv']}
    out.write_text(json.dumps(report,indent=2)+'\n',encoding='utf-8',newline='\n')
    print('PASS: three proposed control paths; lengths', {n:r['centerline_length_mm']for n,r in routes.items()})


if __name__=='__main__':main()
